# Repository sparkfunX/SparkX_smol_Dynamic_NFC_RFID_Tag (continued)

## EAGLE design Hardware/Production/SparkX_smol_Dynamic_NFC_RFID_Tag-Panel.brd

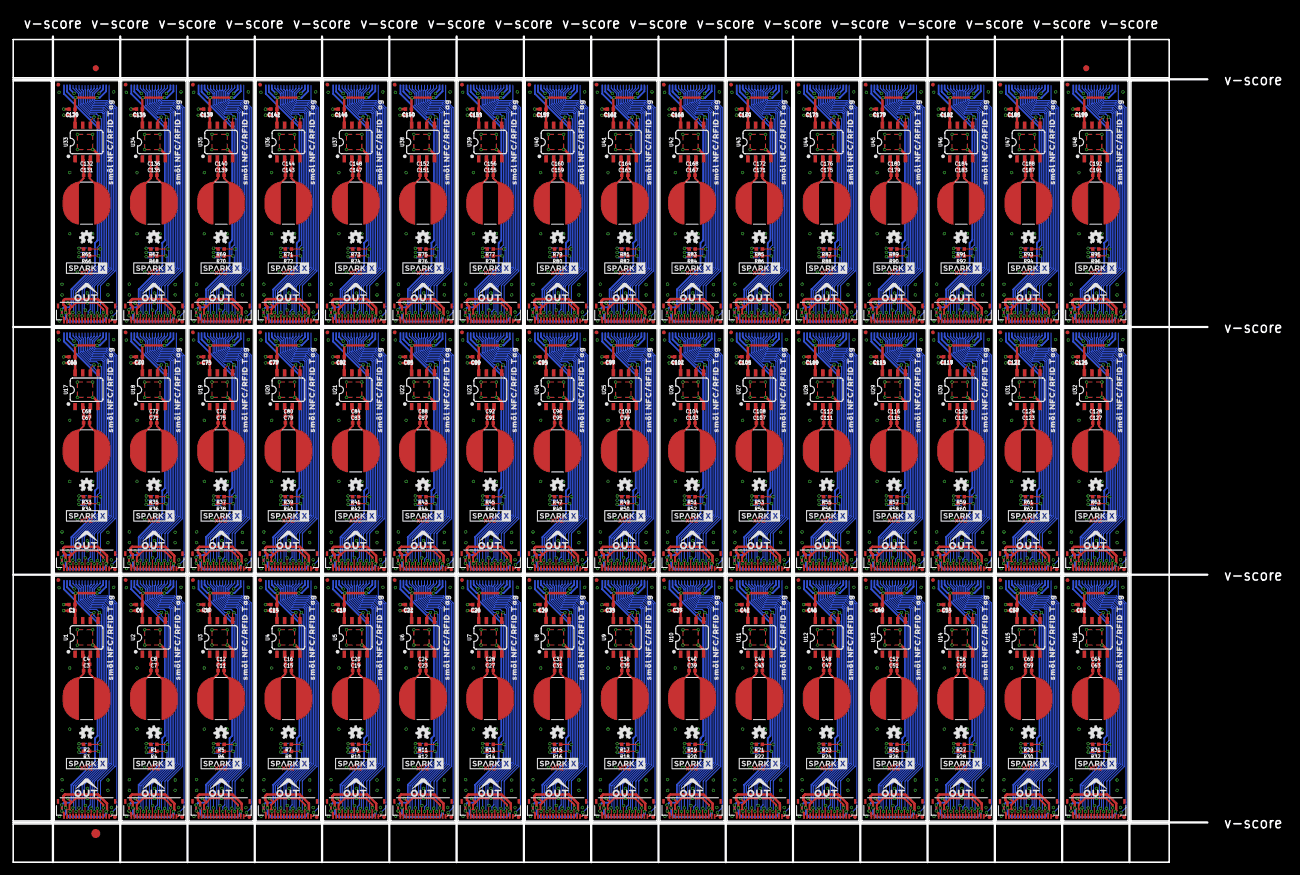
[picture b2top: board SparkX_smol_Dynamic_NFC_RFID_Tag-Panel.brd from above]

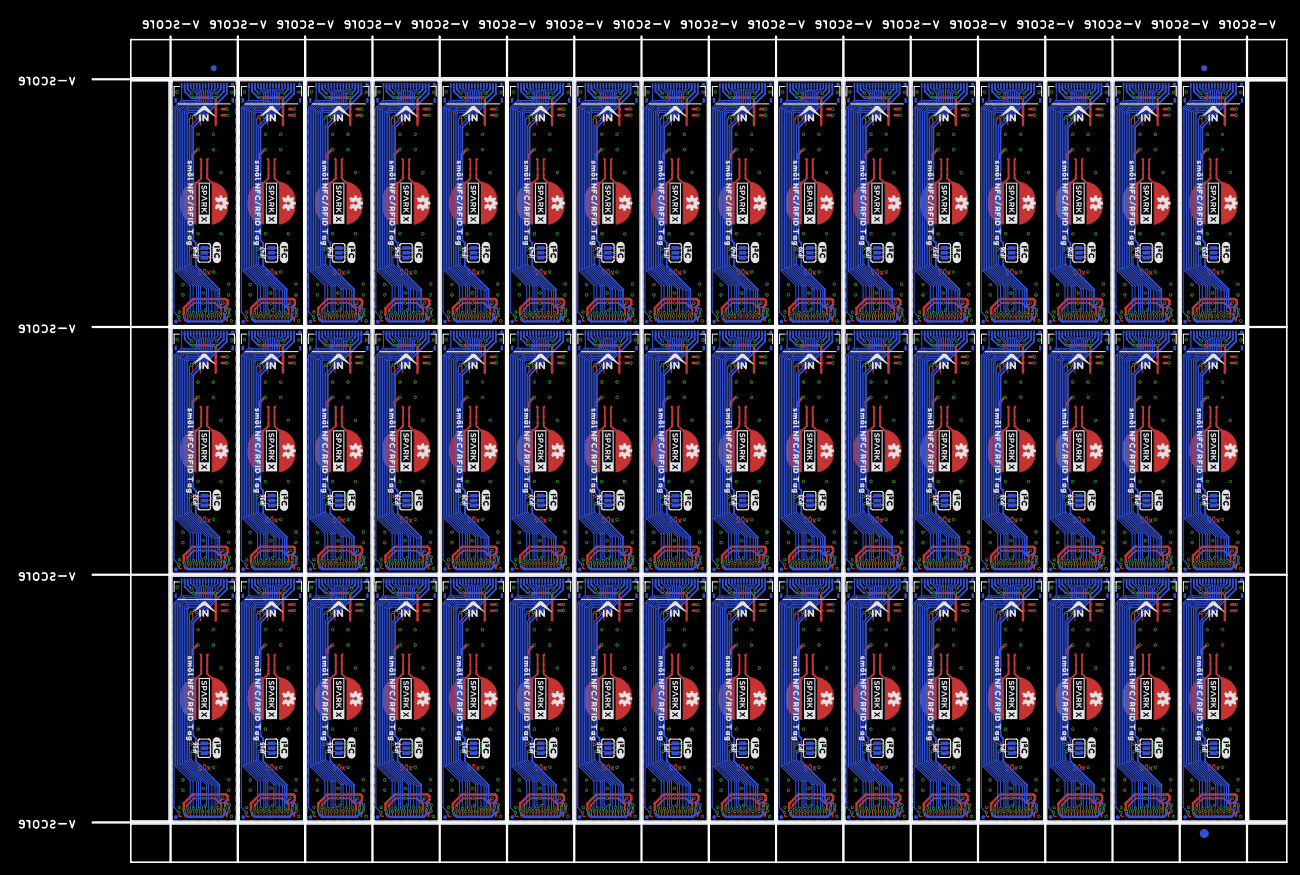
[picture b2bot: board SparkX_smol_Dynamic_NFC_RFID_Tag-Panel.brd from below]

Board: 4 copper layers, 198.4 x 137.2 mm, 1254 parts (483 on the bottom side), 864 nets.

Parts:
ANT, ANT1, ANT2, ANT3, ANT4, ANT5, ANT6, ANT7, ANT8, ANT9, ANT10, ANT11, ANT12, ANT13, ANT14, ANT15, ANT16, ANT17, ANT18, ANT19, ANT20, ANT21, ANT22, ANT23, ANT24, ANT25, ANT26, ANT27, ANT28, ANT29, ANT30, ANT31, ANT32, ANT33, ANT34, ANT35, ANT36, ANT37, ANT38, ANT39, ANT40, ANT41, ANT42, ANT43, ANT44, ANT45, ANT46, ANT47: 4.7μH; W3102
C1, C6, C10, C14, C18, C22, C26, C30, C34, C38, C42, C46, C50, C54, C58, C62, C66, C70, C74, C78, C82, C86, C90, C94, C98, C102, C106, C110, C114, C118, C122, C126, C130, C134, C138, C142, C146, C150, C154, C158, C162, C166, C170, C174, C178, C182, C186, C190: 0.1uF; 0402-TIGHT
C2, C5, C9, C13, C17, C21, C25, C29, C33, C37, C41, C45, C49, C53, C57, C61, C65, C69, C73, C77, C81, C85, C89, C93, C97, C101, C105, C109, C113, C117, C121, C125, C129, C133, C137, C141, C145, C149, C153, C157, C161, C165, C169, C173, C177, C181, C185, C189: 2.2uF; 0402-TIGHT
C3, C7, C11, C15, C19, C23, C27, C31, C35, C39, C43, C47, C51, C55, C59, C63, C67, C71, C75, C79, C83, C87, C91, C95, C99, C103, C107, C111, C115, C119, C123, C127, C131, C135, C139, C143, C147, C151, C155, C159, C163, C167, C171, C175, C179, C183, C187, C191: DNP; 0402-TIGHT_NO_CREAM
C4, C8, C12, C16, C20, C24, C28, C32, C36, C40, C44, C48, C52, C56, C60, C64, C68, C72, C76, C80, C84, C88, C92, C96, C100, C104, C108, C112, C116, C120, C124, C128, C132, C136, C140, C144, C148, C152, C156, C160, C164, C168, C172, C176, C180, C184, C188, C192: 0.5pF; 0402-TIGHT
E$1, E$2, E$3, E$4: FIDUCIAL-1X2
E$5, E$6: FIDUCIAL-1.5X3
FD1, FD2, FD3, FD4, FD5, FD6, FD7, FD8, FD9, FD10, FD11, FD12, FD13, FD14, FD15, FD16, FD17, FD18, FD19, FD20, FD21, FD22, FD23, FD24, FD25, FD26, FD27, FD28, FD29, FD30, FD31, FD32, FD33, FD34, FD35, FD36, FD37, FD38, FD39, FD40, FD41, FD42, FD43, FD44, FD45, FD46, FD47, FD48, FD49, FD50, FD51, FD52, FD53, FD54, FD55, FD56, FD57, FD58, FD59, FD60, FD61, FD62, FD63, FD64, FD65, FD66, FD67, FD68, FD69, FD70, FD71, FD72, FD73, FD74, FD75, FD76, FD77, FD78, FD79, FD80, FD81, FD82, FD83, FD84, FD85, FD86, FD87, FD88, FD89, FD90, FD91, FD92, FD93, FD94, FD95, FD96, FD97, FD98, FD99, FD100, FD101, FD102, FD103, FD104, FD105, FD106, FD107, FD108, FD109, FD110, FD111, FD112, FD113, FD114, FD115, FD116, FD117, FD118, FD119, FD120, FD121, FD122, FD123, FD124, FD125, FD126, FD127, FD128, FD129, FD130, FD131, FD132, FD133, FD134, FD135, FD136, FD137, FD138, FD139, FD140, FD141, FD142, FD143, FD144, FD145, FD146, FD147, FD148, FD149, FD150, FD151, FD152, FD153, FD154, FD155, FD156, FD157, FD158, FD159, FD160, FD161, FD162, FD163, FD164, FD165, FD166, FD167, FD168, FD169, FD170, FD171, FD172, FD173, FD174, FD175, FD176, FD177, FD178, FD179, FD180, FD181, FD182, FD183, FD184, FD185, FD186, FD187, FD188, FD189, FD190, FD191, FD192: FIDUCIALUFIDUCIAL; FIDUCIAL-MICRO
IN, IN1, IN2, IN3, IN4, IN5, IN6, IN7, IN8, IN9, IN10, IN11, IN12, IN13, IN14, IN15, IN16, IN17, IN18, IN19, IN20, IN21, IN22, IN23, IN24, IN25, IN26, IN27, IN28, IN29, IN30, IN31, IN32, IN33, IN34, IN35, IN36, IN37, IN38, IN39, IN40, IN41, IN42, IN43, IN44, IN45, IN46, IN47: FPC_16_0.5MM
JP1, JP2, JP3, JP4, JP5, JP6, JP7, JP8, JP9, JP10, JP11, JP12, JP13, JP14, JP15, JP16, JP17, JP18, JP19, JP20, JP21, JP22, JP23, JP24, JP25, JP26, JP27, JP28, JP29, JP30, JP31, JP32, JP33, JP34, JP35, JP36, JP37, JP38, JP39, JP40, JP41, JP42, JP43, JP44, JP45, JP46, JP47, JP48: JUMPER-SMT_3_NO_SILK; SMT-JUMPER_3_NO_SILK
LOGO1, LOGO2, LOGO3, LOGO4, LOGO5, LOGO6, LOGO7, LOGO8, LOGO9, LOGO10, LOGO11, LOGO12, LOGO13, LOGO14, LOGO15, LOGO16, LOGO17, LOGO18, LOGO19, LOGO20, LOGO21, LOGO22, LOGO23, LOGO24, LOGO25, LOGO26, LOGO27, LOGO28, LOGO29, LOGO30, LOGO31, LOGO32, LOGO33, LOGO34, LOGO35, LOGO36, LOGO37, LOGO38, LOGO39, LOGO40, LOGO41, LOGO42, LOGO43, LOGO44, LOGO45, LOGO46, LOGO47, LOGO48, LOGO49, LOGO50, LOGO51, LOGO52, LOGO53, LOGO54, LOGO55, LOGO56, LOGO57, LOGO58, LOGO59, LOGO60, LOGO61, LOGO62, LOGO63, LOGO64, LOGO65, LOGO66, LOGO67, LOGO68, LOGO69, LOGO70, LOGO71, LOGO72, LOGO73, LOGO74, LOGO75, LOGO76, LOGO77, LOGO78, LOGO79, LOGO80, LOGO81, LOGO82, LOGO83, LOGO84, LOGO85, LOGO86, LOGO87, LOGO88, LOGO89, LOGO90, LOGO91, LOGO92, LOGO93, LOGO94, LOGO95, LOGO96: OSHW-LOGOMINI; OSHW-LOGO-MINI
OUT, OUT1, OUT2, OUT3, OUT4, OUT5, OUT6, OUT7, OUT8, OUT9, OUT10, OUT11, OUT12, OUT13, OUT14, OUT15, OUT16, OUT17, OUT18, OUT19, OUT20, OUT21, OUT22, OUT23, OUT24, OUT25, OUT26, OUT27, OUT28, OUT29, OUT30, OUT31, OUT32, OUT33, OUT34, OUT35, OUT36, OUT37, OUT38, OUT39, OUT40, OUT41, OUT42, OUT43, OUT44, OUT45, OUT46, OUT47: FPC_16_0.5MM
R1, R2, R3, R4, R5, R6, R7, R8, R9, R10, R11, R12, R13, R14, R15, R16, R17, R18, R19, R20, R21, R22, R23, R24, R25, R26, R27, R28, R29, R30, R31, R32, R33, R34, R35, R36, R37, R38, R39, R40, R41, R42, R43, R44, R45, R46, R47, R48, R49, R50, R51, R52, R53, R54, R55, R56, R57, R58, R59, R60, R61, R62, R63, R64, R65, R66, R67, R68, R69, R70, R71, R72, R73, R74, R75, R76, R77, R78, R79, R80, R81, R82, R83, R84, R85, R86, R87, R88, R89, R90, R91, R92, R93, R94, R95, R96: 4.7k; 0402-TIGHT
U1, U2, U3, U4, U5, U6, U7, U8, U9, U10, U11, U12, U13, U14, U15, U16, U17, U18, U19, U20, U21, U22, U23, U24, U25, U26, U27, U28, U29, U30, U31, U32, U33, U34, U35, U36, U37, U38, U39, U40, U41, U42, U43, U44, U45, U46, U47, U48: ST25DV64KC; SO08
U$1, U$6, U$7, U$18, U$19, U$20, U$28, U$29, U$37, U$38, U$46, U$47, U$55, U$56, U$64, U$65, U$73, U$74, U$82, U$83, U$91, U$92, U$100, U$101, U$109, U$110, U$118, U$119, U$127, U$128, U$136, U$137, U$145, U$146, U$154, U$155, U$163, U$164, U$172, U$173, U$181, U$182, U$190, U$191, U$199, U$200, U$208, U$209, U$217, U$218, U$226, U$227, U$235, U$236, U$244, U$245, U$253, U$254, U$262, U$263, U$271, U$272, U$280, U$281, U$289, U$290, U$298, U$299, U$307, U$308, U$316, U$317, U$325, U$326, U$334, U$335, U$343, U$344, U$352, U$353, U$361, U$362, U$370, U$371, U$379, U$380, U$388, U$389, U$397, U$398, U$406, U$407, U$415, U$416, U$424, U$425: SPARKX-LOGO3; SPARKX-SMALL
U$2, U$4, U$14, U$15, U$25, U$26, U$34, U$35, U$43, U$44, U$52, U$53, U$61, U$62, U$70, U$71, U$79, U$80, U$88, U$89, U$97, U$98, U$106, U$107, U$115, U$116, U$124, U$125, U$133, U$134, U$142, U$143, U$151, U$152, U$160, U$161, U$169, U$170, U$178, U$179, U$187, U$188, U$196, U$197, U$205, U$206, U$214, U$215, U$223, U$224, U$232, U$233, U$241, U$242, U$250, U$251, U$259, U$260, U$268, U$269, U$277, U$278, U$286, U$287, U$295, U$296, U$304, U$305, U$313, U$314, U$322, U$323, U$331, U$332, U$340, U$341, U$349, U$350, U$358, U$359, U$367, U$368, U$376, U$377, U$385, U$386, U$394, U$395, U$403, U$404, U$412, U$413, U$421, U$422, U$430, U$431: SM�L_NFC#RFID_TAG0
U$3, U$9, U$12, U$13, U$23, U$24, U$32, U$33, U$41, U$42, U$50, U$51, U$59, U$60, U$68, U$69, U$77, U$78, U$86, U$87, U$95, U$96, U$104, U$105, U$113, U$114, U$122, U$123, U$131, U$132, U$140, U$141, U$149, U$150, U$158, U$159, U$167, U$168, U$176, U$177, U$185, U$186, U$194, U$195, U$203, U$204, U$212, U$213, U$221, U$222, U$230, U$231, U$239, U$240, U$248, U$249, U$257, U$258, U$266, U$267, U$275, U$276, U$284, U$285, U$293, U$294, U$302, U$303, U$311, U$312, U$320, U$321, U$329, U$330, U$338, U$339, U$347, U$348, U$356, U$357, U$365, U$366, U$374, U$375, U$383, U$384, U$392, U$393, U$401, U$402, U$410, U$411, U$419, U$420, U$428, U$429: SMOL_LOGOSMALL; SMOL_SMALL
U$5, U$16, U$27, U$36, U$45, U$54, U$63, U$72, U$81, U$90, U$99, U$108, U$117, U$126, U$135, U$144, U$153, U$162, U$171, U$180, U$189, U$198, U$207, U$216, U$225, U$234, U$243, U$252, U$261, U$270, U$279, U$288, U$297, U$306, U$315, U$324, U$333, U$342, U$351, U$360, U$369, U$378, U$387, U$396, U$405, U$414, U$423, U$432: #I�C#0
U$8, U$10, U$21, U$30, U$39, U$48, U$57, U$66, U$75, U$84, U$93, U$102, U$111, U$120, U$129, U$138, U$147, U$156, U$165, U$174, U$183, U$192, U$201, U$210, U$219, U$228, U$237, U$246, U$255, U$264, U$273, U$282, U$291, U$300, U$309, U$318, U$327, U$336, U$345, U$354, U$363, U$372, U$381, U$390, U$399, U$408, U$417, U$426: IN0
U$11, U$17, U$22, U$31, U$40, U$49, U$58, U$67, U$76, U$85, U$94, U$103, U$112, U$121, U$130, U$139, U$148, U$157, U$166, U$175, U$184, U$193, U$202, U$211, U$220, U$229, U$238, U$247, U$256, U$265, U$274, U$283, U$292, U$301, U$310, U$319, U$328, U$337, U$346, U$355, U$364, U$373, U$382, U$391, U$400, U$409, U$418, U$427: OUT0

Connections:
3.3V: C1.1, C2.1, IN.2, IN.15, JP1.2, OUT.2, OUT.15, U1.8
3.3V1: C5.1, C6.1, IN1.2, IN1.15, JP2.2, OUT1.2, OUT1.15, U2.8
3.3V2: C9.1, C10.1, IN2.2, IN2.15, JP3.2, OUT2.2, OUT2.15, U3.8
3.3V3: C13.1, C14.1, IN3.2, IN3.15, JP4.2, OUT3.2, OUT3.15, U4.8
3.3V4: C17.1, C18.1, IN4.2, IN4.15, JP5.2, OUT4.2, OUT4.15, U5.8
3.3V5: C21.1, C22.1, IN5.2, IN5.15, JP6.2, OUT5.2, OUT5.15, U6.8
3.3V6: C25.1, C26.1, IN6.2, IN6.15, JP7.2, OUT6.2, OUT6.15, U7.8
3.3V7: C29.1, C30.1, IN7.2, IN7.15, JP8.2, OUT7.2, OUT7.15, U8.8
3.3V8: C33.1, C34.1, IN8.2, IN8.15, JP9.2, OUT8.2, OUT8.15, U9.8
3.3V9: C37.1, C38.1, IN9.2, IN9.15, JP10.2, OUT9.2, OUT9.15, U10.8
3.3V10: C41.1, C42.1, IN10.2, IN10.15, JP11.2, OUT10.2, OUT10.15, U11.8
3.3V11: C45.1, C46.1, IN11.2, IN11.15, JP12.2, OUT11.2, OUT11.15, U12.8
3.3V12: C49.1, C50.1, IN12.2, IN12.15, JP13.2, OUT12.2, OUT12.15, U13.8
3.3V13: C53.1, C54.1, IN13.2, IN13.15, JP14.2, OUT13.2, OUT13.15, U14.8
3.3V14: C57.1, C58.1, IN14.2, IN14.15, JP15.2, OUT14.2, OUT14.15, U15.8
3.3V15: C61.1, C62.1, IN15.2, IN15.15, JP16.2, OUT15.2, OUT15.15, U16.8
3.3V16: C65.1, C66.1, IN16.2, IN16.15, JP17.2, OUT16.2, OUT16.15, U17.8
3.3V17: C69.1, C70.1, IN17.2, IN17.15, JP18.2, OUT17.2, OUT17.15, U18.8
3.3V18: C73.1, C74.1, IN18.2, IN18.15, JP19.2, OUT18.2, OUT18.15, U19.8
3.3V19: C77.1, C78.1, IN19.2, IN19.15, JP20.2, OUT19.2, OUT19.15, U20.8
3.3V20: C81.1, C82.1, IN20.2, IN20.15, JP21.2, OUT20.2, OUT20.15, U21.8
3.3V21: C85.1, C86.1, IN21.2, IN21.15, JP22.2, OUT21.2, OUT21.15, U22.8
3.3V22: C89.1, C90.1, IN22.2, IN22.15, JP23.2, OUT22.2, OUT22.15, U23.8
3.3V23: C93.1, C94.1, IN23.2, IN23.15, JP24.2, OUT23.2, OUT23.15, U24.8
3.3V24: C97.1, C98.1, IN24.2, IN24.15, JP25.2, OUT24.2, OUT24.15, U25.8
3.3V25: C101.1, C102.1, IN25.2, IN25.15, JP26.2, OUT25.2, OUT25.15, U26.8
3.3V26: C105.1, C106.1, IN26.2, IN26.15, JP27.2, OUT26.2, OUT26.15, U27.8
3.3V27: C109.1, C110.1, IN27.2, IN27.15, JP28.2, OUT27.2, OUT27.15, U28.8
3.3V28: C113.1, C114.1, IN28.2, IN28.15, JP29.2, OUT28.2, OUT28.15, U29.8
3.3V29: C117.1, C118.1, IN29.2, IN29.15, JP30.2, OUT29.2, OUT29.15, U30.8
3.3V30: C121.1, C122.1, IN30.2, IN30.15, JP31.2, OUT30.2, OUT30.15, U31.8
3.3V31: C125.1, C126.1, IN31.2, IN31.15, JP32.2, OUT31.2, OUT31.15, U32.8
3.3V32: C129.1, C130.1, IN32.2, IN32.15, JP33.2, OUT32.2, OUT32.15, U33.8
3.3V33: C133.1, C134.1, IN33.2, IN33.15, JP34.2, OUT33.2, OUT33.15, U34.8
3.3V34: C137.1, C138.1, IN34.2, IN34.15, JP35.2, OUT34.2, OUT34.15, U35.8
3.3V35: C141.1, C142.1, IN35.2, IN35.15, JP36.2, OUT35.2, OUT35.15, U36.8
3.3V36: C145.1, C146.1, IN36.2, IN36.15, JP37.2, OUT36.2, OUT36.15, U37.8
3.3V37: C149.1, C150.1, IN37.2, IN37.15, JP38.2, OUT37.2, OUT37.15, U38.8
3.3V38: C153.1, C154.1, IN38.2, IN38.15, JP39.2, OUT38.2, OUT38.15, U39.8
3.3V39: C157.1, C158.1, IN39.2, IN39.15, JP40.2, OUT39.2, OUT39.15, U40.8
3.3V40: C161.1, C162.1, IN40.2, IN40.15, JP41.2, OUT40.2, OUT40.15, U41.8
3.3V41: C165.1, C166.1, IN41.2, IN41.15, JP42.2, OUT41.2, OUT41.15, U42.8
3.3V42: C169.1, C170.1, IN42.2, IN42.15, JP43.2, OUT42.2, OUT42.15, U43.8
3.3V43: C173.1, C174.1, IN43.2, IN43.15, JP44.2, OUT43.2, OUT43.15, U44.8
3.3V44: C177.1, C178.1, IN44.2, IN44.15, JP45.2, OUT44.2, OUT44.15, U45.8
3.3V45: C181.1, C182.1, IN45.2, IN45.15, JP46.2, OUT45.2, OUT45.15, U46.8
3.3V46: C185.1, C186.1, IN46.2, IN46.15, JP47.2, OUT46.2, OUT46.15, U47.8
3.3V47: C189.1, C190.1, IN47.2, IN47.15, JP48.2, OUT47.2, OUT47.15, U48.8
CIPO: IN.6, OUT.6
CIPO1: IN1.6, OUT1.6
CIPO2: IN2.6, OUT2.6
CIPO3: IN3.6, OUT3.6
CIPO4: IN4.6, OUT4.6
CIPO5: IN5.6, OUT5.6
CIPO6: IN6.6, OUT6.6
CIPO7: IN7.6, OUT7.6
CIPO8: IN8.6, OUT8.6
CIPO9: IN9.6, OUT9.6
CIPO10: IN10.6, OUT10.6
CIPO11: IN11.6, OUT11.6
CIPO12: IN12.6, OUT12.6
CIPO13: IN13.6, OUT13.6
CIPO14: IN14.6, OUT14.6
CIPO15: IN15.6, OUT15.6
CIPO16: IN16.6, OUT16.6
CIPO17: IN17.6, OUT17.6
CIPO18: IN18.6, OUT18.6
CIPO19: IN19.6, OUT19.6
CIPO20: IN20.6, OUT20.6
CIPO21: IN21.6, OUT21.6
CIPO22: IN22.6, OUT22.6
CIPO23: IN23.6, OUT23.6
CIPO24: IN24.6, OUT24.6
CIPO25: IN25.6, OUT25.6
CIPO26: IN26.6, OUT26.6
CIPO27: IN27.6, OUT27.6
CIPO28: IN28.6, OUT28.6
CIPO29: IN29.6, OUT29.6
CIPO30: IN30.6, OUT30.6
CIPO31: IN31.6, OUT31.6
CIPO32: IN32.6, OUT32.6
CIPO33: IN33.6, OUT33.6
CIPO34: IN34.6, OUT34.6
CIPO35: IN35.6, OUT35.6
CIPO36: IN36.6, OUT36.6
CIPO37: IN37.6, OUT37.6
CIPO38: IN38.6, OUT38.6
CIPO39: IN39.6, OUT39.6
CIPO40: IN40.6, OUT40.6
CIPO41: IN41.6, OUT41.6
CIPO42: IN42.6, OUT42.6
CIPO43: IN43.6, OUT43.6
CIPO44: IN44.6, OUT44.6
CIPO45: IN45.6, OUT45.6
CIPO46: IN46.6, OUT46.6
CIPO47: IN47.6, OUT47.6
COPI: IN.5, OUT.5
COPI1: IN1.5, OUT1.5
COPI2: IN2.5, OUT2.5
COPI3: IN3.5, OUT3.5
COPI4: IN4.5, OUT4.5
COPI5: IN5.5, OUT5.5
COPI6: IN6.5, OUT6.5
COPI7: IN7.5, OUT7.5
COPI8: IN8.5, OUT8.5
COPI9: IN9.5, OUT9.5
COPI10: IN10.5, OUT10.5
COPI11: IN11.5, OUT11.5
COPI12: IN12.5, OUT12.5
COPI13: IN13.5, OUT13.5
COPI14: IN14.5, OUT14.5
COPI15: IN15.5, OUT15.5
COPI16: IN16.5, OUT16.5
COPI17: IN17.5, OUT17.5
COPI18: IN18.5, OUT18.5
COPI19: IN19.5, OUT19.5
COPI20: IN20.5, OUT20.5
COPI21: IN21.5, OUT21.5
COPI22: IN22.5, OUT22.5
COPI23: IN23.5, OUT23.5
COPI24: IN24.5, OUT24.5
COPI25: IN25.5, OUT25.5
COPI26: IN26.5, OUT26.5
COPI27: IN27.5, OUT27.5
COPI28: IN28.5, OUT28.5
COPI29: IN29.5, OUT29.5
COPI30: IN30.5, OUT30.5
COPI31: IN31.5, OUT31.5
COPI32: IN32.5, OUT32.5
COPI33: IN33.5, OUT33.5
COPI34: IN34.5, OUT34.5
COPI35: IN35.5, OUT35.5
COPI36: IN36.5, OUT36.5
COPI37: IN37.5, OUT37.5
COPI38: IN38.5, OUT38.5
COPI39: IN39.5, OUT39.5
COPI40: IN40.5, OUT40.5
COPI41: IN41.5, OUT41.5
COPI42: IN42.5, OUT42.5
COPI43: IN43.5, OUT43.5
COPI44: IN44.5, OUT44.5
COPI45: IN45.5, OUT45.5
COPI46: IN46.5, OUT46.5
COPI47: IN47.5, OUT47.5
CS0: IN.7, OUT.7
CS1: IN.8, OUT.8
CS2: IN.9, OUT.9
CS3: IN1.7, OUT1.7
CS4: IN1.8, OUT1.8
CS5: IN1.9, OUT1.9
CS6: IN2.7, OUT2.7
CS7: IN2.8, OUT2.8
CS8: IN2.9, OUT2.9
CS9: IN3.7, OUT3.7
CS10: IN3.8, OUT3.8
CS11: IN3.9, OUT3.9
CS12: IN4.7, OUT4.7
CS13: IN4.8, OUT4.8
CS14: IN4.9, OUT4.9
CS15: IN5.7, OUT5.7
CS16: IN5.8, OUT5.8
CS17: IN5.9, OUT5.9
CS18: IN6.7, OUT6.7
CS19: IN6.8, OUT6.8
CS20: IN6.9, OUT6.9
CS21: IN7.7, OUT7.7
CS22: IN7.8, OUT7.8
CS23: IN7.9, OUT7.9
CS24: IN8.7, OUT8.7
CS25: IN8.8, OUT8.8
CS26: IN8.9, OUT8.9
CS27: IN9.7, OUT9.7
CS28: IN9.8, OUT9.8
CS29: IN9.9, OUT9.9
CS30: IN10.7, OUT10.7
CS31: IN10.8, OUT10.8
CS32: IN10.9, OUT10.9
CS33: IN11.7, OUT11.7
CS34: IN11.8, OUT11.8
CS35: IN11.9, OUT11.9
CS36: IN12.7, OUT12.7
CS37: IN12.8, OUT12.8
CS38: IN12.9, OUT12.9
CS39: IN13.7, OUT13.7
CS40: IN13.8, OUT13.8
CS41: IN13.9, OUT13.9
CS42: IN14.7, OUT14.7
CS43: IN14.8, OUT14.8
CS44: IN14.9, OUT14.9
CS45: IN15.7, OUT15.7
CS46: IN15.8, OUT15.8
CS47: IN15.9, OUT15.9
CS48: IN16.7, OUT16.7
CS49: IN16.8, OUT16.8
CS50: IN16.9, OUT16.9
CS51: IN17.7, OUT17.7
CS52: IN17.8, OUT17.8
CS53: IN17.9, OUT17.9
CS54: IN18.7, OUT18.7
CS55: IN18.8, OUT18.8
CS56: IN18.9, OUT18.9
CS57: IN19.7, OUT19.7
CS58: IN19.8, OUT19.8
CS59: IN19.9, OUT19.9
CS60: IN20.7, OUT20.7
CS61: IN20.8, OUT20.8
CS62: IN20.9, OUT20.9
CS63: IN21.7, OUT21.7
CS64: IN21.8, OUT21.8
CS65: IN21.9, OUT21.9
CS66: IN22.7, OUT22.7
CS67: IN22.8, OUT22.8
CS68: IN22.9, OUT22.9
CS69: IN23.7, OUT23.7
CS70: IN23.8, OUT23.8
CS71: IN23.9, OUT23.9
CS72: IN24.7, OUT24.7
CS73: IN24.8, OUT24.8
CS74: IN24.9, OUT24.9
CS75: IN25.7, OUT25.7
CS76: IN25.8, OUT25.8
CS77: IN25.9, OUT25.9
CS78: IN26.7, OUT26.7
CS79: IN26.8, OUT26.8
CS80: IN26.9, OUT26.9
CS81: IN27.7, OUT27.7
CS82: IN27.8, OUT27.8
CS83: IN27.9, OUT27.9
CS84: IN28.7, OUT28.7
CS85: IN28.8, OUT28.8
CS86: IN28.9, OUT28.9
CS87: IN29.7, OUT29.7
CS88: IN29.8, OUT29.8
CS89: IN29.9, OUT29.9
CS90: IN30.7, OUT30.7
CS91: IN30.8, OUT30.8
CS92: IN30.9, OUT30.9
CS93: IN31.7, OUT31.7
CS94: IN31.8, OUT31.8
CS95: IN31.9, OUT31.9
CS96: IN32.7, OUT32.7
CS97: IN32.8, OUT32.8
CS98: IN32.9, OUT32.9
CS99: IN33.7, OUT33.7
CS100: IN33.8, OUT33.8
CS101: IN33.9, OUT33.9
CS102: IN34.7, OUT34.7
CS103: IN34.8, OUT34.8
CS104: IN34.9, OUT34.9
CS105: IN35.7, OUT35.7
CS106: IN35.8, OUT35.8
CS107: IN35.9, OUT35.9
CS108: IN36.7, OUT36.7
CS109: IN36.8, OUT36.8
CS110: IN36.9, OUT36.9
CS111: IN37.7, OUT37.7
CS112: IN37.8, OUT37.8
CS113: IN37.9, OUT37.9
CS114: IN38.7, OUT38.7
CS115: IN38.8, OUT38.8
CS116: IN38.9, OUT38.9
CS117: IN39.7, OUT39.7
CS118: IN39.8, OUT39.8
CS119: IN39.9, OUT39.9
CS120: IN40.7, OUT40.7
CS121: IN40.8, OUT40.8
CS122: IN40.9, OUT40.9
CS123: IN41.7, OUT41.7
CS124: IN41.8, OUT41.8
CS125: IN41.9, OUT41.9
CS126: IN42.7, OUT42.7
CS127: IN42.8, OUT42.8
CS128: IN42.9, OUT42.9
CS129: IN43.7, OUT43.7
CS130: IN43.8, OUT43.8
CS131: IN43.9, OUT43.9
CS132: IN44.7, OUT44.7
CS133: IN44.8, OUT44.8
CS134: IN44.9, OUT44.9
CS135: IN45.7, OUT45.7
CS136: IN45.8, OUT45.8
CS137: IN45.9, OUT45.9
CS138: IN46.7, OUT46.7
CS139: IN46.8, OUT46.8
CS140: IN46.9, OUT46.9
CS141: IN47.7, OUT47.7
CS142: IN47.8, OUT47.8
CS143: IN47.9, OUT47.9
GND: C1.2, C2.2, IN.3, IN.14, OUT.3, OUT.14, U1.4
GND1: C5.2, C6.2, IN1.3, IN1.14, OUT1.3, OUT1.14, U2.4
GND2: C9.2, C10.2, IN2.3, IN2.14, OUT2.3, OUT2.14, U3.4
GND3: C13.2, C14.2, IN3.3, IN3.14, OUT3.3, OUT3.14, U4.4
GND4: C17.2, C18.2, IN4.3, IN4.14, OUT4.3, OUT4.14, U5.4
GND5: C21.2, C22.2, IN5.3, IN5.14, OUT5.3, OUT5.14, U6.4
GND6: C25.2, C26.2, IN6.3, IN6.14, OUT6.3, OUT6.14, U7.4
GND7: C29.2, C30.2, IN7.3, IN7.14, OUT7.3, OUT7.14, U8.4
GND8: C33.2, C34.2, IN8.3, IN8.14, OUT8.3, OUT8.14, U9.4
GND9: C37.2, C38.2, IN9.3, IN9.14, OUT9.3, OUT9.14, U10.4
GND10: C41.2, C42.2, IN10.3, IN10.14, OUT10.3, OUT10.14, U11.4
GND11: C45.2, C46.2, IN11.3, IN11.14, OUT11.3, OUT11.14, U12.4
GND12: C49.2, C50.2, IN12.3, IN12.14, OUT12.3, OUT12.14, U13.4
GND13: C53.2, C54.2, IN13.3, IN13.14, OUT13.3, OUT13.14, U14.4
GND14: C57.2, C58.2, IN14.3, IN14.14, OUT14.3, OUT14.14, U15.4
GND15: C61.2, C62.2, IN15.3, IN15.14, OUT15.3, OUT15.14, U16.4
GND16: C65.2, C66.2, IN16.3, IN16.14, OUT16.3, OUT16.14, U17.4
GND17: C69.2, C70.2, IN17.3, IN17.14, OUT17.3, OUT17.14, U18.4
GND18: C73.2, C74.2, IN18.3, IN18.14, OUT18.3, OUT18.14, U19.4
GND19: C77.2, C78.2, IN19.3, IN19.14, OUT19.3, OUT19.14, U20.4
GND20: C81.2, C82.2, IN20.3, IN20.14, OUT20.3, OUT20.14, U21.4
GND21: C85.2, C86.2, IN21.3, IN21.14, OUT21.3, OUT21.14, U22.4
GND22: C89.2, C90.2, IN22.3, IN22.14, OUT22.3, OUT22.14, U23.4
GND23: C93.2, C94.2, IN23.3, IN23.14, OUT23.3, OUT23.14, U24.4
GND24: C97.2, C98.2, IN24.3, IN24.14, OUT24.3, OUT24.14, U25.4
GND25: C101.2, C102.2, IN25.3, IN25.14, OUT25.3, OUT25.14, U26.4
GND26: C105.2, C106.2, IN26.3, IN26.14, OUT26.3, OUT26.14, U27.4
GND27: C109.2, C110.2, IN27.3, IN27.14, OUT27.3, OUT27.14, U28.4
GND28: C113.2, C114.2, IN28.3, IN28.14, OUT28.3, OUT28.14, U29.4
GND29: C117.2, C118.2, IN29.3, IN29.14, OUT29.3, OUT29.14, U30.4
GND30: C121.2, C122.2, IN30.3, IN30.14, OUT30.3, OUT30.14, U31.4
GND31: C125.2, C126.2, IN31.3, IN31.14, OUT31.3, OUT31.14, U32.4
GND32: C129.2, C130.2, IN32.3, IN32.14, OUT32.3, OUT32.14, U33.4
GND33: C133.2, C134.2, IN33.3, IN33.14, OUT33.3, OUT33.14, U34.4
GND34: C137.2, C138.2, IN34.3, IN34.14, OUT34.3, OUT34.14, U35.4
GND35: C141.2, C142.2, IN35.3, IN35.14, OUT35.3, OUT35.14, U36.4
GND36: C145.2, C146.2, IN36.3, IN36.14, OUT36.3, OUT36.14, U37.4
GND37: C149.2, C150.2, IN37.3, IN37.14, OUT37.3, OUT37.14, U38.4
GND38: C153.2, C154.2, IN38.3, IN38.14, OUT38.3, OUT38.14, U39.4
GND39: C157.2, C158.2, IN39.3, IN39.14, OUT39.3, OUT39.14, U40.4
GND40: C161.2, C162.2, IN40.3, IN40.14, OUT40.3, OUT40.14, U41.4
GND41: C165.2, C166.2, IN41.3, IN41.14, OUT41.3, OUT41.14, U42.4
GND42: C169.2, C170.2, IN42.3, IN42.14, OUT42.3, OUT42.14, U43.4
GND43: C173.2, C174.2, IN43.3, IN43.14, OUT43.3, OUT43.14, U44.4
GND44: C177.2, C178.2, IN44.3, IN44.14, OUT44.3, OUT44.14, U45.4
GND45: C181.2, C182.2, IN45.3, IN45.14, OUT45.3, OUT45.14, U46.4
GND46: C185.2, C186.2, IN46.3, IN46.14, OUT46.3, OUT46.14, U47.4
GND47: C189.2, C190.2, IN47.3, IN47.14, OUT47.3, OUT47.14, U48.4
GPIO0: IN.10, OUT.10
GPIO1: IN.11, OUT.11
GPIO2: IN1.10, OUT1.10
GPIO3: IN1.11, OUT1.11
GPIO4: IN2.10, OUT2.10
GPIO5: IN2.11, OUT2.11
GPIO6: IN3.10, OUT3.10
GPIO7: IN3.11, OUT3.11
GPIO8: IN4.10, OUT4.10
GPIO9: IN4.11, OUT4.11
GPIO10: IN5.10, OUT5.10
GPIO11: IN5.11, OUT5.11
GPIO12: IN6.10, OUT6.10
GPIO13: IN6.11, OUT6.11
GPIO14: IN7.10, OUT7.10
GPIO15: IN7.11, OUT7.11
GPIO16: IN8.10, OUT8.10
GPIO17: IN8.11, OUT8.11
GPIO18: IN9.10, OUT9.10
GPIO19: IN9.11, OUT9.11
GPIO20: IN10.10, OUT10.10
GPIO21: IN10.11, OUT10.11
GPIO22: IN11.10, OUT11.10
GPIO23: IN11.11, OUT11.11
GPIO24: IN12.10, OUT12.10
GPIO25: IN12.11, OUT12.11
GPIO26: IN13.10, OUT13.10
GPIO27: IN13.11, OUT13.11
GPIO28: IN14.10, OUT14.10
GPIO29: IN14.11, OUT14.11
GPIO30: IN15.10, OUT15.10
GPIO31: IN15.11, OUT15.11
GPIO32: IN16.10, OUT16.10
GPIO33: IN16.11, OUT16.11
GPIO34: IN17.10, OUT17.10
GPIO35: IN17.11, OUT17.11
GPIO36: IN18.10, OUT18.10
GPIO37: IN18.11, OUT18.11
GPIO38: IN19.10, OUT19.10
GPIO39: IN19.11, OUT19.11
GPIO40: IN20.10, OUT20.10
GPIO41: IN20.11, OUT20.11
GPIO42: IN21.10, OUT21.10
GPIO43: IN21.11, OUT21.11
GPIO44: IN22.10, OUT22.10
GPIO45: IN22.11, OUT22.11
GPIO46: IN23.10, OUT23.10
GPIO47: IN23.11, OUT23.11
GPIO48: IN24.10, OUT24.10
GPIO49: IN24.11, OUT24.11
GPIO50: IN25.10, OUT25.10
GPIO51: IN25.11, OUT25.11
GPIO52: IN26.10, OUT26.10
GPIO53: IN26.11, OUT26.11
GPIO54: IN27.10, OUT27.10
GPIO55: IN27.11, OUT27.11
GPIO56: IN28.10, OUT28.10
GPIO57: IN28.11, OUT28.11
GPIO58: IN29.10, OUT29.10
GPIO59: IN29.11, OUT29.11
GPIO60: IN30.10, OUT30.10
GPIO61: IN30.11, OUT30.11
GPIO62: IN31.10, OUT31.10
GPIO63: IN31.11, OUT31.11
GPIO64: IN32.10, OUT32.10
GPIO65: IN32.11, OUT32.11
GPIO66: IN33.10, OUT33.10
GPIO67: IN33.11, OUT33.11
GPIO68: IN34.10, OUT34.10
GPIO69: IN34.11, OUT34.11
GPIO70: IN35.10, OUT35.10
GPIO71: IN35.11, OUT35.11
GPIO72: IN36.10, OUT36.10
GPIO73: IN36.11, OUT36.11
GPIO74: IN37.10, OUT37.10
GPIO75: IN37.11, OUT37.11
GPIO76: IN38.10, OUT38.10
GPIO77: IN38.11, OUT38.11
GPIO78: IN39.10, OUT39.10
GPIO79: IN39.11, OUT39.11
GPIO80: IN40.10, OUT40.10
GPIO81: IN40.11, OUT40.11
GPIO82: IN41.10, OUT41.10
GPIO83: IN41.11, OUT41.11
GPIO84: IN42.10, OUT42.10
GPIO85: IN42.11, OUT42.11
GPIO86: IN43.10, OUT43.10
GPIO87: IN43.11, OUT43.11
GPIO88: IN44.10, OUT44.10
GPIO89: IN44.11, OUT44.11
GPIO90: IN45.10, OUT45.10
GPIO91: IN45.11, OUT45.11
GPIO92: IN46.10, OUT46.10
GPIO93: IN46.11, OUT46.11
GPIO94: IN47.10, OUT47.10
GPIO95: IN47.11, OUT47.11
unnamed: ANT.2, C3.2, C4.2, U1.3
unnamed: ANT.1, C3.1, C4.1, U1.2
unnamed: JP1.3, R2.2
unnamed: JP1.1, R3.2
unnamed: ANT1.2, C7.2, C8.2, U2.3
unnamed: ANT1.1, C7.1, C8.1, U2.2
unnamed: JP2.3, R1.2
unnamed: JP2.1, R4.2
unnamed: ANT2.2, C11.2, C12.2, U3.3
unnamed: ANT2.1, C11.1, C12.1, U3.2
unnamed: JP3.3, R5.2
unnamed: JP3.1, R6.2
unnamed: ANT3.2, C15.2, C16.2, U4.3
unnamed: ANT3.1, C15.1, C16.1, U4.2
unnamed: JP4.3, R7.2
unnamed: JP4.1, R8.2
unnamed: ANT4.2, C19.2, C20.2, U5.3
unnamed: ANT4.1, C19.1, C20.1, U5.2
unnamed: JP5.3, R9.2
unnamed: JP5.1, R10.2
unnamed: ANT5.2, C23.2, C24.2, U6.3
unnamed: ANT5.1, C23.1, C24.1, U6.2
unnamed: JP6.3, R11.2
unnamed: JP6.1, R12.2
unnamed: ANT6.2, C27.2, C28.2, U7.3
unnamed: ANT6.1, C27.1, C28.1, U7.2
unnamed: JP7.3, R13.2
unnamed: JP7.1, R14.2
unnamed: ANT7.2, C31.2, C32.2, U8.3
unnamed: ANT7.1, C31.1, C32.1, U8.2
unnamed: JP8.3, R15.2
unnamed: JP8.1, R16.2
unnamed: ANT8.2, C35.2, C36.2, U9.3
unnamed: ANT8.1, C35.1, C36.1, U9.2
unnamed: JP9.3, R17.2
unnamed: JP9.1, R18.2
unnamed: ANT9.2, C39.2, C40.2, U10.3
unnamed: ANT9.1, C39.1, C40.1, U10.2
unnamed: JP10.3, R19.2
unnamed: JP10.1, R20.2
unnamed: ANT10.2, C43.2, C44.2, U11.3
unnamed: ANT10.1, C43.1, C44.1, U11.2
unnamed: JP11.3, R21.2
unnamed: JP11.1, R22.2
unnamed: ANT11.2, C47.2, C48.2, U12.3
unnamed: ANT11.1, C47.1, C48.1, U12.2
unnamed: JP12.3, R23.2
unnamed: JP12.1, R24.2
unnamed: ANT12.2, C51.2, C52.2, U13.3
unnamed: ANT12.1, C51.1, C52.1, U13.2
unnamed: JP13.3, R25.2
unnamed: JP13.1, R26.2
unnamed: ANT13.2, C55.2, C56.2, U14.3
unnamed: ANT13.1, C55.1, C56.1, U14.2
unnamed: JP14.3, R27.2
unnamed: JP14.1, R28.2
unnamed: ANT14.2, C59.2, C60.2, U15.3
unnamed: ANT14.1, C59.1, C60.1, U15.2
unnamed: JP15.3, R29.2
unnamed: JP15.1, R30.2
unnamed: ANT15.2, C63.2, C64.2, U16.3
unnamed: ANT15.1, C63.1, C64.1, U16.2
unnamed: JP16.3, R31.2
unnamed: JP16.1, R32.2
unnamed: ANT16.2, C67.2, C68.2, U17.3
unnamed: ANT16.1, C67.1, C68.1, U17.2
unnamed: JP17.3, R33.2
unnamed: JP17.1, R34.2
unnamed: ANT17.2, C71.2, C72.2, U18.3
unnamed: ANT17.1, C71.1, C72.1, U18.2
unnamed: JP18.3, R35.2
unnamed: JP18.1, R36.2
unnamed: ANT18.2, C75.2, C76.2, U19.3
unnamed: ANT18.1, C75.1, C76.1, U19.2
unnamed: JP19.3, R37.2
unnamed: JP19.1, R38.2
unnamed: ANT19.2, C79.2, C80.2, U20.3
unnamed: ANT19.1, C79.1, C80.1, U20.2
unnamed: JP20.3, R39.2
unnamed: JP20.1, R40.2
unnamed: ANT20.2, C83.2, C84.2, U21.3
unnamed: ANT20.1, C83.1, C84.1, U21.2
unnamed: JP21.3, R41.2
unnamed: JP21.1, R42.2
unnamed: ANT21.2, C87.2, C88.2, U22.3
unnamed: ANT21.1, C87.1, C88.1, U22.2
unnamed: JP22.3, R43.2
unnamed: JP22.1, R44.2
unnamed: ANT22.2, C91.2, C92.2, U23.3
unnamed: ANT22.1, C91.1, C92.1, U23.2
unnamed: JP23.3, R45.2
unnamed: JP23.1, R46.2
unnamed: ANT23.2, C95.2, C96.2, U24.3
unnamed: ANT23.1, C95.1, C96.1, U24.2
unnamed: JP24.3, R47.2
unnamed: JP24.1, R48.2
unnamed: ANT24.2, C99.2, C100.2, U25.3
unnamed: ANT24.1, C99.1, C100.1, U25.2
unnamed: JP25.3, R49.2
unnamed: JP25.1, R50.2
unnamed: ANT25.2, C103.2, C104.2, U26.3
unnamed: ANT25.1, C103.1, C104.1, U26.2
unnamed: JP26.3, R51.2
unnamed: JP26.1, R52.2
unnamed: ANT26.2, C107.2, C108.2, U27.3
unnamed: ANT26.1, C107.1, C108.1, U27.2
unnamed: JP27.3, R53.2
unnamed: JP27.1, R54.2
unnamed: ANT27.2, C111.2, C112.2, U28.3
unnamed: ANT27.1, C111.1, C112.1, U28.2
unnamed: JP28.3, R55.2
unnamed: JP28.1, R56.2
unnamed: ANT28.2, C115.2, C116.2, U29.3
unnamed: ANT28.1, C115.1, C116.1, U29.2
unnamed: JP29.3, R57.2
unnamed: JP29.1, R58.2
unnamed: ANT29.2, C119.2, C120.2, U30.3
unnamed: ANT29.1, C119.1, C120.1, U30.2
unnamed: JP30.3, R59.2
unnamed: JP30.1, R60.2
unnamed: ANT30.2, C123.2, C124.2, U31.3
unnamed: ANT30.1, C123.1, C124.1, U31.2
unnamed: JP31.3, R61.2
unnamed: JP31.1, R62.2
unnamed: ANT31.2, C127.2, C128.2, U32.3
unnamed: ANT31.1, C127.1, C128.1, U32.2
unnamed: JP32.3, R63.2
unnamed: JP32.1, R64.2
unnamed: ANT32.2, C131.2, C132.2, U33.3
unnamed: ANT32.1, C131.1, C132.1, U33.2
unnamed: JP33.3, R65.2
unnamed: JP33.1, R66.2
unnamed: ANT33.2, C135.2, C136.2, U34.3
unnamed: ANT33.1, C135.1, C136.1, U34.2
unnamed: JP34.3, R67.2
unnamed: JP34.1, R68.2
unnamed: ANT34.2, C139.2, C140.2, U35.3
unnamed: ANT34.1, C139.1, C140.1, U35.2
unnamed: JP35.3, R69.2
unnamed: JP35.1, R70.2
unnamed: ANT35.2, C143.2, C144.2, U36.3
unnamed: ANT35.1, C143.1, C144.1, U36.2
unnamed: JP36.3, R71.2
unnamed: JP36.1, R72.2
unnamed: ANT36.2, C147.2, C148.2, U37.3
unnamed: ANT36.1, C147.1, C148.1, U37.2
unnamed: JP37.3, R73.2
unnamed: JP37.1, R74.2
unnamed: ANT37.2, C151.2, C152.2, U38.3
unnamed: ANT37.1, C151.1, C152.1, U38.2
unnamed: JP38.3, R75.2
unnamed: JP38.1, R76.2
unnamed: ANT38.2, C155.2, C156.2, U39.3
unnamed: ANT38.1, C155.1, C156.1, U39.2
unnamed: JP39.3, R77.2
unnamed: JP39.1, R78.2
unnamed: ANT39.2, C159.2, C160.2, U40.3
unnamed: ANT39.1, C159.1, C160.1, U40.2
unnamed: JP40.3, R79.2
unnamed: JP40.1, R80.2
unnamed: ANT40.2, C163.2, C164.2, U41.3
unnamed: ANT40.1, C163.1, C164.1, U41.2
unnamed: JP41.3, R81.2
unnamed: JP41.1, R82.2
unnamed: ANT41.2, C167.2, C168.2, U42.3
unnamed: ANT41.1, C167.1, C168.1, U42.2
unnamed: JP42.3, R83.2
unnamed: JP42.1, R84.2
unnamed: ANT42.2, C171.2, C172.2, U43.3
unnamed: ANT42.1, C171.1, C172.1, U43.2
unnamed: JP43.3, R85.2
unnamed: JP43.1, R86.2
unnamed: ANT43.2, C175.2, C176.2, U44.3
unnamed: ANT43.1, C175.1, C176.1, U44.2
unnamed: JP44.3, R87.2
unnamed: JP44.1, R88.2
unnamed: ANT44.2, C179.2, C180.2, U45.3
unnamed: ANT44.1, C179.1, C180.1, U45.2
unnamed: JP45.3, R89.2
unnamed: JP45.1, R90.2
unnamed: ANT45.2, C183.2, C184.2, U46.3
unnamed: ANT45.1, C183.1, C184.1, U46.2
unnamed: JP46.3, R91.2
unnamed: JP46.1, R92.2
unnamed: ANT46.2, C187.2, C188.2, U47.3
unnamed: ANT46.1, C187.1, C188.1, U47.2
unnamed: JP47.3, R93.2
unnamed: JP47.1, R94.2
unnamed: ANT47.2, C191.2, C192.2, U48.3
unnamed: ANT47.1, C191.1, C192.1, U48.2
unnamed: JP48.3, R95.2
unnamed: JP48.1, R96.2
PROC_PWR_EN: IN.1, OUT.1
PROC_PWR_EN1: IN1.1, OUT1.1
PROC_PWR_EN2: IN2.1, OUT2.1
PROC_PWR_EN3: IN3.1, OUT3.1
PROC_PWR_EN4: IN4.1, OUT4.1
PROC_PWR_EN5: IN5.1, OUT5.1
PROC_PWR_EN6: IN6.1, OUT6.1
PROC_PWR_EN7: IN7.1, OUT7.1
PROC_PWR_EN8: IN8.1, OUT8.1
PROC_PWR_EN9: IN9.1, OUT9.1
PROC_PWR_EN10: IN10.1, OUT10.1
PROC_PWR_EN11: IN11.1, OUT11.1
PROC_PWR_EN12: IN12.1, OUT12.1
PROC_PWR_EN13: IN13.1, OUT13.1
PROC_PWR_EN14: IN14.1, OUT14.1
PROC_PWR_EN15: IN15.1, OUT15.1
PROC_PWR_EN16: IN16.1, OUT16.1
PROC_PWR_EN17: IN17.1, OUT17.1
PROC_PWR_EN18: IN18.1, OUT18.1
PROC_PWR_EN19: IN19.1, OUT19.1
PROC_PWR_EN20: IN20.1, OUT20.1
PROC_PWR_EN21: IN21.1, OUT21.1
PROC_PWR_EN22: IN22.1, OUT22.1
PROC_PWR_EN23: IN23.1, OUT23.1
PROC_PWR_EN24: IN24.1, OUT24.1
PROC_PWR_EN25: IN25.1, OUT25.1
PROC_PWR_EN26: IN26.1, OUT26.1
PROC_PWR_EN27: IN27.1, OUT27.1
PROC_PWR_EN28: IN28.1, OUT28.1
PROC_PWR_EN29: IN29.1, OUT29.1
PROC_PWR_EN30: IN30.1, OUT30.1
PROC_PWR_EN31: IN31.1, OUT31.1
PROC_PWR_EN32: IN32.1, OUT32.1
PROC_PWR_EN33: IN33.1, OUT33.1
PROC_PWR_EN34: IN34.1, OUT34.1
PROC_PWR_EN35: IN35.1, OUT35.1
PROC_PWR_EN36: IN36.1, OUT36.1
PROC_PWR_EN37: IN37.1, OUT37.1
PROC_PWR_EN38: IN38.1, OUT38.1
PROC_PWR_EN39: IN39.1, OUT39.1
PROC_PWR_EN40: IN40.1, OUT40.1
PROC_PWR_EN41: IN41.1, OUT41.1
PROC_PWR_EN42: IN42.1, OUT42.1
PROC_PWR_EN43: IN43.1, OUT43.1
PROC_PWR_EN44: IN44.1, OUT44.1
PROC_PWR_EN45: IN45.1, OUT45.1
PROC_PWR_EN46: IN46.1, OUT46.1
PROC_PWR_EN47: IN47.1, OUT47.1
SCL: IN.13, OUT.13, R3.1, U1.6
SCL1: IN1.13, OUT1.13, R4.1, U2.6
SCL2: IN2.13, OUT2.13, R6.1, U3.6
SCL3: IN3.13, OUT3.13, R8.1, U4.6
SCL4: IN4.13, OUT4.13, R10.1, U5.6
SCL5: IN5.13, OUT5.13, R12.1, U6.6
SCL6: IN6.13, OUT6.13, R14.1, U7.6
SCL7: IN7.13, OUT7.13, R16.1, U8.6
SCL8: IN8.13, OUT8.13, R18.1, U9.6
SCL9: IN9.13, OUT9.13, R20.1, U10.6
SCL10: IN10.13, OUT10.13, R22.1, U11.6
SCL11: IN11.13, OUT11.13, R24.1, U12.6
SCL12: IN12.13, OUT12.13, R26.1, U13.6
SCL13: IN13.13, OUT13.13, R28.1, U14.6
SCL14: IN14.13, OUT14.13, R30.1, U15.6
SCL15: IN15.13, OUT15.13, R32.1, U16.6
SCL16: IN16.13, OUT16.13, R34.1, U17.6
SCL17: IN17.13, OUT17.13, R36.1, U18.6
SCL18: IN18.13, OUT18.13, R38.1, U19.6
SCL19: IN19.13, OUT19.13, R40.1, U20.6
SCL20: IN20.13, OUT20.13, R42.1, U21.6
SCL21: IN21.13, OUT21.13, R44.1, U22.6
SCL22: IN22.13, OUT22.13, R46.1, U23.6
SCL23: IN23.13, OUT23.13, R48.1, U24.6
SCL24: IN24.13, OUT24.13, R50.1, U25.6
SCL25: IN25.13, OUT25.13, R52.1, U26.6
SCL26: IN26.13, OUT26.13, R54.1, U27.6
SCL27: IN27.13, OUT27.13, R56.1, U28.6
SCL28: IN28.13, OUT28.13, R58.1, U29.6
SCL29: IN29.13, OUT29.13, R60.1, U30.6
SCL30: IN30.13, OUT30.13, R62.1, U31.6
SCL31: IN31.13, OUT31.13, R64.1, U32.6
SCL32: IN32.13, OUT32.13, R66.1, U33.6
SCL33: IN33.13, OUT33.13, R68.1, U34.6
SCL34: IN34.13, OUT34.13, R70.1, U35.6
SCL35: IN35.13, OUT35.13, R72.1, U36.6
SCL36: IN36.13, OUT36.13, R74.1, U37.6
SCL37: IN37.13, OUT37.13, R76.1, U38.6
SCL38: IN38.13, OUT38.13, R78.1, U39.6
SCL39: IN39.13, OUT39.13, R80.1, U40.6
SCL40: IN40.13, OUT40.13, R82.1, U41.6
SCL41: IN41.13, OUT41.13, R84.1, U42.6
SCL42: IN42.13, OUT42.13, R86.1, U43.6
SCL43: IN43.13, OUT43.13, R88.1, U44.6
SCL44: IN44.13, OUT44.13, R90.1, U45.6
SCL45: IN45.13, OUT45.13, R92.1, U46.6
SCL46: IN46.13, OUT46.13, R94.1, U47.6
SCL47: IN47.13, OUT47.13, R96.1, U48.6
SCLK: IN.4, OUT.4
SCLK1: IN1.4, OUT1.4
SCLK2: IN2.4, OUT2.4
SCLK3: IN3.4, OUT3.4
SCLK4: IN4.4, OUT4.4
SCLK5: IN5.4, OUT5.4
SCLK6: IN6.4, OUT6.4
SCLK7: IN7.4, OUT7.4
SCLK8: IN8.4, OUT8.4
SCLK9: IN9.4, OUT9.4
SCLK10: IN10.4, OUT10.4
SCLK11: IN11.4, OUT11.4
SCLK12: IN12.4, OUT12.4
SCLK13: IN13.4, OUT13.4
SCLK14: IN14.4, OUT14.4
SCLK15: IN15.4, OUT15.4
SCLK16: IN16.4, OUT16.4
SCLK17: IN17.4, OUT17.4
SCLK18: IN18.4, OUT18.4
SCLK19: IN19.4, OUT19.4
SCLK20: IN20.4, OUT20.4
SCLK21: IN21.4, OUT21.4
SCLK22: IN22.4, OUT22.4
SCLK23: IN23.4, OUT23.4
SCLK24: IN24.4, OUT24.4
SCLK25: IN25.4, OUT25.4
SCLK26: IN26.4, OUT26.4
SCLK27: IN27.4, OUT27.4
SCLK28: IN28.4, OUT28.4
SCLK29: IN29.4, OUT29.4
SCLK30: IN30.4, OUT30.4
SCLK31: IN31.4, OUT31.4
SCLK32: IN32.4, OUT32.4
SCLK33: IN33.4, OUT33.4
SCLK34: IN34.4, OUT34.4
SCLK35: IN35.4, OUT35.4
SCLK36: IN36.4, OUT36.4
SCLK37: IN37.4, OUT37.4
SCLK38: IN38.4, OUT38.4
SCLK39: IN39.4, OUT39.4
SCLK40: IN40.4, OUT40.4
SCLK41: IN41.4, OUT41.4
SCLK42: IN42.4, OUT42.4
SCLK43: IN43.4, OUT43.4
SCLK44: IN44.4, OUT44.4
SCLK45: IN45.4, OUT45.4
SCLK46: IN46.4, OUT46.4
SCLK47: IN47.4, OUT47.4
SDA: IN.12, OUT.12, R2.1, U1.5
SDA1: IN1.12, OUT1.12, R1.1, U2.5
SDA2: IN2.12, OUT2.12, R5.1, U3.5
SDA3: IN3.12, OUT3.12, R7.1, U4.5
SDA4: IN4.12, OUT4.12, R9.1, U5.5
SDA5: IN5.12, OUT5.12, R11.1, U6.5
SDA6: IN6.12, OUT6.12, R13.1, U7.5
SDA7: IN7.12, OUT7.12, R15.1, U8.5
SDA8: IN8.12, OUT8.12, R17.1, U9.5
SDA9: IN9.12, OUT9.12, R19.1, U10.5
SDA10: IN10.12, OUT10.12, R21.1, U11.5
SDA11: IN11.12, OUT11.12, R23.1, U12.5
SDA12: IN12.12, OUT12.12, R25.1, U13.5
SDA13: IN13.12, OUT13.12, R27.1, U14.5
SDA14: IN14.12, OUT14.12, R29.1, U15.5
SDA15: IN15.12, OUT15.12, R31.1, U16.5
SDA16: IN16.12, OUT16.12, R33.1, U17.5
SDA17: IN17.12, OUT17.12, R35.1, U18.5
SDA18: IN18.12, OUT18.12, R37.1, U19.5
SDA19: IN19.12, OUT19.12, R39.1, U20.5
SDA20: IN20.12, OUT20.12, R41.1, U21.5
SDA21: IN21.12, OUT21.12, R43.1, U22.5
SDA22: IN22.12, OUT22.12, R45.1, U23.5
SDA23: IN23.12, OUT23.12, R47.1, U24.5
SDA24: IN24.12, OUT24.12, R49.1, U25.5
SDA25: IN25.12, OUT25.12, R51.1, U26.5
SDA26: IN26.12, OUT26.12, R53.1, U27.5
SDA27: IN27.12, OUT27.12, R55.1, U28.5
SDA28: IN28.12, OUT28.12, R57.1, U29.5
SDA29: IN29.12, OUT29.12, R59.1, U30.5
SDA30: IN30.12, OUT30.12, R61.1, U31.5
SDA31: IN31.12, OUT31.12, R63.1, U32.5
SDA32: IN32.12, OUT32.12, R65.1, U33.5
SDA33: IN33.12, OUT33.12, R67.1, U34.5
SDA34: IN34.12, OUT34.12, R69.1, U35.5
SDA35: IN35.12, OUT35.12, R71.1, U36.5
SDA36: IN36.12, OUT36.12, R73.1, U37.5
SDA37: IN37.12, OUT37.12, R75.1, U38.5
SDA38: IN38.12, OUT38.12, R77.1, U39.5
SDA39: IN39.12, OUT39.12, R79.1, U40.5
SDA40: IN40.12, OUT40.12, R81.1, U41.5
SDA41: IN41.12, OUT41.12, R83.1, U42.5
SDA42: IN42.12, OUT42.12, R85.1, U43.5
SDA43: IN43.12, OUT43.12, R87.1, U44.5
SDA44: IN44.12, OUT44.12, R89.1, U45.5
SDA45: IN45.12, OUT45.12, R91.1, U46.5
SDA46: IN46.12, OUT46.12, R93.1, U47.5
SDA47: IN47.12, OUT47.12, R95.1, U48.5
V_USB: IN.16, OUT.16
V_USB1: IN1.16, OUT1.16
V_USB2: IN2.16, OUT2.16
V_USB3: IN3.16, OUT3.16
V_USB4: IN4.16, OUT4.16
V_USB5: IN5.16, OUT5.16
V_USB6: IN6.16, OUT6.16
V_USB7: IN7.16, OUT7.16
V_USB8: IN8.16, OUT8.16
V_USB9: IN9.16, OUT9.16
V_USB10: IN10.16, OUT10.16
V_USB11: IN11.16, OUT11.16
V_USB12: IN12.16, OUT12.16
V_USB13: IN13.16, OUT13.16
V_USB14: IN14.16, OUT14.16
V_USB15: IN15.16, OUT15.16
V_USB16: IN16.16, OUT16.16
V_USB17: IN17.16, OUT17.16
V_USB18: IN18.16, OUT18.16
V_USB19: IN19.16, OUT19.16
V_USB20: IN20.16, OUT20.16
V_USB21: IN21.16, OUT21.16
V_USB22: IN22.16, OUT22.16
V_USB23: IN23.16, OUT23.16
V_USB24: IN24.16, OUT24.16
V_USB25: IN25.16, OUT25.16
V_USB26: IN26.16, OUT26.16
V_USB27: IN27.16, OUT27.16
V_USB28: IN28.16, OUT28.16
V_USB29: IN29.16, OUT29.16
V_USB30: IN30.16, OUT30.16
V_USB31: IN31.16, OUT31.16
V_USB32: IN32.16, OUT32.16
V_USB33: IN33.16, OUT33.16
V_USB34: IN34.16, OUT34.16
V_USB35: IN35.16, OUT35.16
V_USB36: IN36.16, OUT36.16
V_USB37: IN37.16, OUT37.16
V_USB38: IN38.16, OUT38.16
V_USB39: IN39.16, OUT39.16
V_USB40: IN40.16, OUT40.16
V_USB41: IN41.16, OUT41.16
V_USB42: IN42.16, OUT42.16
V_USB43: IN43.16, OUT43.16
V_USB44: IN44.16, OUT44.16
V_USB45: IN45.16, OUT45.16
V_USB46: IN46.16, OUT46.16
V_USB47: IN47.16, OUT47.16

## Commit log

2021-11-09 Add README
2021-11-09 Add Eagle files
2021-11-10 Change to 4-layer
2021-11-11 x02: change to W3102 antenna
2021-11-11 Add antenna datasheet
2022-09-16 Add product image
